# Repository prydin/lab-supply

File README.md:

# Linear 0-30V, 2A lab power supply

## Disclaimer

This supply has been built and tested and does work. However, I am a hobbyist doing this to learn. You are
welcome to follow along, but keep the experimental status in mind and always exercise caution when dealing
with electricity!

## Abstract

This project aims to design a high-performance, high-stability microcontroller-based lab power supply. I am
mostly doing this to learn, but also because I'm tired of cheap switchmode power supplies delivering power
riddled with RF noise.

## Principle of operation

### High voltage section

The high voltage section is very simple and consists of a regular AC inlet with a safety capacitor across it.
There is a 3A fuse in series with the hot lead and a two pole mains switch. The transformer is a 24V/4A unit
with a 12V center tap. Once rectified, the voltage reaches about 36V at my location. Mains ground is connected
to the chassis as well as the ground output terminal.

### Analog secion

32-36V AC enters the circuit at the `AC1` and `AC2` terminals and gets rectified and smoothed into approximately
36-40V DC. This voltage is then pre-regulated down to 32V through `Q3` which is gets its voltage reference the
backwards bias of `D3`. This voltage is used to power the opamps. The `CNT` input is the transformer center tap,
which should be around 15V and is used to create the +12V and +5V voltages.

The `U1D` opamp acts as a voltage regulation amplifier and expects a control voltage between 0-4.096V on its postive input. The feedback loop is tuned
to 7.32x amplification, resulting in an output voltage ranging from 0-30V. The Darlington pair at `Q3` acts
as a emitter follower current amplifier.

Current regulation is based on a high-side current sensing resistor, `R27`. The differential voltage across the
current sense resistor is amplified to a 0-2.5V signal using an INA225 current sense amplifier. This voltage is
then sent to the positivie input of `U1A`. The control circuitry feeds a 0-4.096V signal
to the `V_ISET` input, which is scaled down to 0-2.5V through a resistor network. This voltage is then fed to the
negative input of `U1A`. When the voltage from the current sense amplifier goes above the control voltage on the negative input,
the opamp will source current to Q2, which brings the base on Q3 low until the current is limited to the
set value. `Q3` is needed since we want to keep R24 relatively low to avoid voltage drop at high output currents,
while making sure `U1A` isn't sourcing or sinking too much current. `Q1` acts as a simple switch for turning on
the current limit indicator LED.

### Digital section

The digital section is based on a Adafruit ItsyBitsy 5V, which is essentially an Atmel ATMega 32u4 with some
support circuitry. This was chosen to simplify the design and keep everything as through hole. The digital
section is responsible for feeding the `V_VSET` and `V_ISET` voltages to the the analog section, as well
as measuring and presenting actual voltages and currents.

A key component is the LMZ4040DBZ voltage reference, which provides a stable 4.096V reference used by the
rest of the circuit.

The control voltages are generated by an MPC4922 12-bit DAC and fed directly to the analog section. The user
sets the desired voltage and current using two rotary encoders which can be pushed to switch between a "fine"
and "coarse" mode.

The output voltage of the supply is measured by an MCP3202 ADC through a voltage divider network to bring the
voltage down to 0-4.096V. Further overvoltage protection is offered by the `D12` clamping diode. Current is
measured in a similar way, but since that signal is in the 0-1V range, it is first amplified 4.096x by `U1B`.
This signal is also clamped to the 4.096V reference through `D10`.

## Controls

### Current and voltage

Current and voltage are controlled using two rotary encoders. Pressing the knob switches between coarse and fine
mode. In coarse mode, a blinking cursor will indicate the least significant digit subject to change by turning
the knob.

### Enable/disable

The enable switch enables or disables the output. Notice that this is a "soft" disable that's simply shorting
the posisitive terminal on the voltage regulation opamp to ground. Thus, the output is NOT electrically isolated
from the rest of the circuit.

### Lock mode

When the lock switch is activated, voltage and current output are locked to their current values. The user can
still change the settings, but they are not acted upon. When the switch is flipped, the voltage and current
output is changed to the current setting. This is useful when a user is carefully dialing in new settings
without changing the output while turning the knobs. When locked mode is activated, the "->" symbol between
set and actual values on the display is changed to "LCK".

## Grounding

This power supply is designed to be floating, i.e. it is isolated from ground. If the user needs either
output (plus or minus) to be grounded, they may simply short it to ground using a ground bar or patch
wire. Since the supply uses high side current sense, accidental shorts to ground should not cause damage.

## Physical design and enclosure

### PCB design

This is my very first PCB design and there are many beginners mistakes present in the design. However, it
does work. If I ever redesign this, I would make the +36V path shorter, for example. There are also some
questionable component placements. As with any open source project, you are encouraged to improve on it!

### Enclosure

I opted for a cheap sheet metal/plastic box that is widely available on sites like Ali Express and Amazon.
It works well, but the metal is fairly thin and tends to flex when unplugging the leads.

### Cooling

The TIP142 output transistor requires good cooling. I opted for a simple $9 AMD CPU cooler and bolted the
transistor and the 7805 regulator to it. I'm currently using isolating pads for the TIP142, but I'm not
entirely happy with the heat transfer. I might remove that, although I'm not sure I like to have unregulated 36V
exposed inside the case. The fan is PWM controlled using a simple temperature curve algorithm.

### Rotary encoders and switches

The rotary encoders and switches (with exception of the mains switch) are all cheap Amazon products and work
well so far.

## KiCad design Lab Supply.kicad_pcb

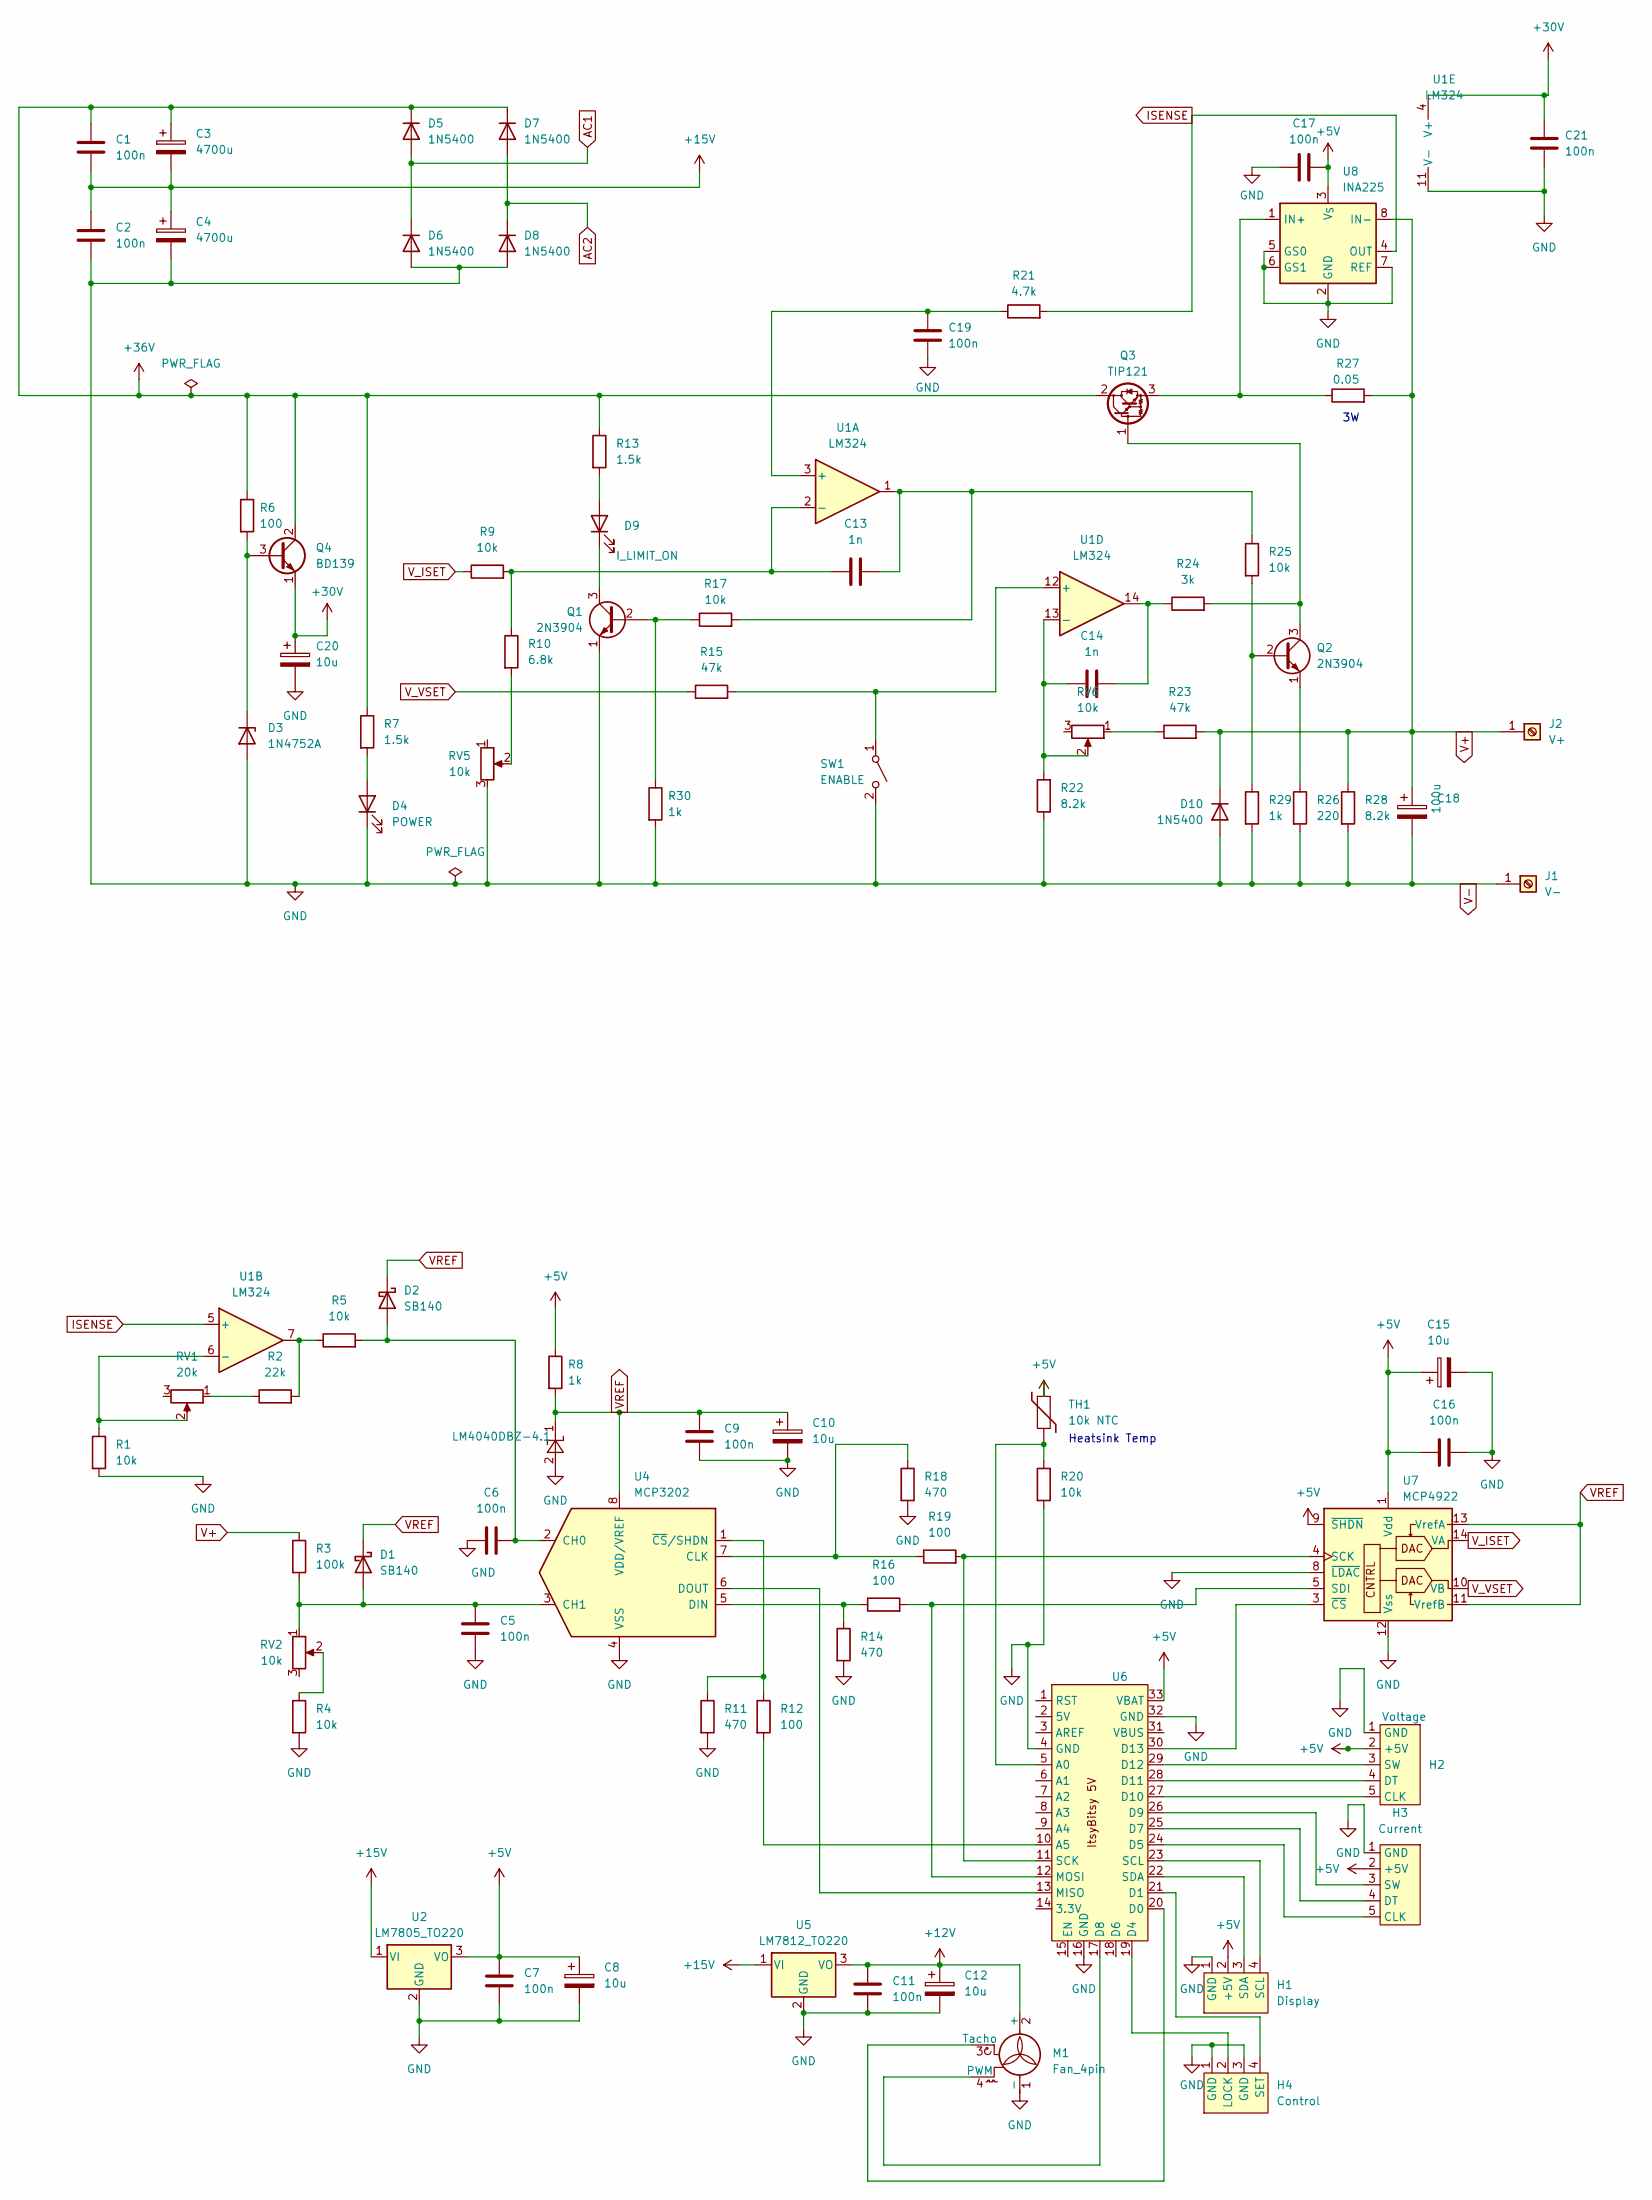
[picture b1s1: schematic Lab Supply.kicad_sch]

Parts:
C1, C2, C5, C6, C7, C9, C11, C16, C17, C19, C21: 100n; C_Disc_D3.4mm_W2.1mm_P2.50mm
C3, C4: 4700u; CP_Radial_D18.0mm_P7.50mm
C8, C10, C12, C15, C20: 10u; CP_Radial_D4.0mm_P1.50mm
C13, C14: 1n; C_Disc_D3.4mm_W2.1mm_P2.50mm
C18: 100u; CP_Radial_D8.0mm_P3.50mm
D1, D2: SB140; D_DO-41_SOD81_P10.16mm_Horizontal
D3: 1N4752A; D_DO-41_SOD81_P5.08mm_Vertical_KathodeUp
D4: POWER; PinHeader_1x02_P2.54mm_Vertical
D5, D6, D7, D8, D10: 1N5400; D_DO-201AD_P12.70mm_Horizontal
D9: I_LIMIT_ON; PinHeader_1x02_P2.54mm_Vertical
H1: Display; PinHeader_1x04_P2.54mm_Vertical
H2: Voltage; PinHeader_1x05_P2.54mm_Vertical
H3: Current; PinHeader_1x05_P2.54mm_Vertical
H4: Control; PinHeader_1x04_P2.54mm_Vertical
J1: V-
J2: V+
M1: Fan_4pin; Molex_KK-254_AE-6410-04A_1x04_P2.54mm_Vertical
Q1, Q2: 2N3904; TO-92_Inline
Q3: TIP121; TO-220-3_Vertical
Q4: BD139; TO-126-3_Vertical
R1, R4, R5, R9, R17, R20, R25: 10k; R_Axial_DIN0204_L3.6mm_D1.6mm_P7.62mm_Horizontal
R2: 22k; R_Axial_DIN0204_L3.6mm_D1.6mm_P7.62mm_Horizontal
R3: 100k; R_Axial_DIN0204_L3.6mm_D1.6mm_P7.62mm_Horizontal
R6, R12, R16, R19: 100; R_Axial_DIN0204_L3.6mm_D1.6mm_P7.62mm_Horizontal
R7, R13: 1.5k; R_Axial_DIN0204_L3.6mm_D1.6mm_P7.62mm_Horizontal
R8, R29, R30: 1k; R_Axial_DIN0204_L3.6mm_D1.6mm_P7.62mm_Horizontal
R10: 6.8k; R_Axial_DIN0204_L3.6mm_D1.6mm_P7.62mm_Horizontal
R11, R14, R18: 470; R_Axial_DIN0204_L3.6mm_D1.6mm_P7.62mm_Horizontal
R15, R23: 47k; R_Axial_DIN0204_L3.6mm_D1.6mm_P7.62mm_Horizontal
R21: 4.7k; R_Axial_DIN0204_L3.6mm_D1.6mm_P7.62mm_Horizontal
R22, R28: 8.2k; R_Axial_DIN0204_L3.6mm_D1.6mm_P7.62mm_Horizontal
R24: 3k; R_Axial_DIN0204_L3.6mm_D1.6mm_P7.62mm_Horizontal
R26: 220; R_Axial_DIN0204_L3.6mm_D1.6mm_P7.62mm_Horizontal
R27: 0.05; R_Axial_DIN0207_L6.3mm_D2.5mm_P10.16mm_Horizontal
RV1: 20k; TRIM_3362P-1-253LF
RV2, RV5, RV6: 10k; TRIM_3362P-1-253LF
SW1: ENABLE; PinHeader_1x02_P2.54mm_Vertical
TH1: 10k NTC; PinHeader_1x02_P2.54mm_Vertical
U1: LM324; DIP-14_W7.62mm
U2: LM7805_TO220; TO-220-3_Vertical
U3: LM4040DBZ-4.1; TO-92_HandSolder
U4: MCP3202; DIP-8_W7.62mm
U5: LM7812_TO220; TO-220-3_Vertical
U6: Itsy Bitsy 5V
U7: MCP4922; DIP-14_W7.62mm
U8: INA225; VSSOP-8_3.0x3.0mm_P0.65mm

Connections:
+5V: C7.1, C8.1, C15.1, C16.1, C17.2, H1.2 (+5V), H2.2 (+5V), H3.2 (+5V), R8.1, TH1.1, U2.3 (VO), U6.33 (VBAT), U7.1 (Vdd), U7.9 (~SHDN), U8.3 (V_{S})
+12V: C11.1, C12.1, M1.2 (+), U5.3 (VO)
+15V: C1.2, C2.1, C3.2, C4.1, J1.2, U2.1 (VI), U5.1 (VI)
+28V: C20.1, C21.1, Q4.1 (E), U1.4 (V+)
+36V: C1.1, C3.1, D5.1 (K), D7.1 (K), Q3.2 (C), Q4.2 (C), R6.1, R7.1, R13.1
AC2: D7.2 (A), D8.1 (K), J1.3
ISENSE: R21.2, U1.5 (+), U8.4 (OUT)
unnamed: C13.2, R17.2, R25.1, U1.1
unnamed: C14.1, R24.1, U1.14
unnamed: C5.1, D1.2 (A), R3.2, RV2.1, U4.3 (CH1)
unnamed: C6.2, D2.2 (A), R5.2, U4.2 (CH0)
unnamed: D3.1 (K), Q4.3 (B), R6.2
unnamed: D4.2 (A), R7.2
unnamed: D9.2 (A), R13.2
unnamed: D9.1 (K), Q1.3 (C)
unnamed: H1.4 (SCL), U6.23 (SCL)
unnamed: H1.3 (SDA), U6.22 (SDA)
unnamed: H2.5 (CLK), U6.27 (D10)
unnamed: H2.4 (DT), U6.28 (D11)
unnamed: H2.3 (SW), U6.29 (D12)
unnamed: H3.5 (CLK), U6.24 (D5)
unnamed: H3.4 (DT), U6.25 (D7)
unnamed: H3.3 (SW), U6.26 (D9)
unnamed: H4.2 (LOCK), U6.19 (D4)
unnamed: H4.4 (SET), U6.21 (D1)
unnamed: M1.4 (PWM), U6.17 (D8)
unnamed: M1.3 (Tacho), U6.20 (D0)
unnamed: Q1.2 (B), R17.1, R30.1
unnamed: Q2.2 (B), R25.2, R29.1
unnamed: Q2.3 (C), Q3.1 (B), R24.2
unnamed: Q2.1 (E), R26.1
unnamed: Q3.3 (E), R27.1, U8.1 (IN+)
unnamed: R2.1, RV1.1
unnamed: R2.2, R5.1, U1.7
unnamed: R4.1, RV2.2
unnamed: R10.2, RV5.2
unnamed: R23.1, RV6.1
unnamed: R15.2, SW1.1 (A), U1.12 (+)
unnamed: C19.1, R21.1, U1.3 (+)
unnamed: C13.1, R9.2, R10.1, U1.2 (-)
unnamed: R1.1, RV1.2, U1.6 (-)
unnamed: C14.2, R22.2, RV6.2, U1.13 (-)
unnamed: R18.1, R19.1, U4.7 (CLK)
unnamed: R14.1, R16.1, U4.5 (DIN)
unnamed: U4.6 (DOUT), U6.13 (MISO)
unnamed: R11.1, R12.1, U4.1 (~CS/SHDN)
unnamed: R20.1, TH1.2, U6.5 (A0)
unnamed: R12.2, U6.10 (A5)
unnamed: U6.30 (D13), U7.3 (~CS)
unnamed: R16.2, U6.12 (MOSI), U7.5 (SDI)
unnamed: R19.2, U6.11 (SCK), U7.4 (SCK)
V+: C18.1, D10.1 (K), J2.1, R3.1, R23.2, R27.2, R28.1, U8.8 (IN-); also elsewhere on the board
VREF: C9.1, C10.1, D1.1 (K), D2.1 (K), R8.2, U3.1 (K), U4.8 (VDD/VREF), U7.11 (VrefB), U7.13 (VrefA)
V_ISET: R9.1, U7.14 (VA)
V_VSET: R15.1, U7.10 (VB)

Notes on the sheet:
Heatsink Temp

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
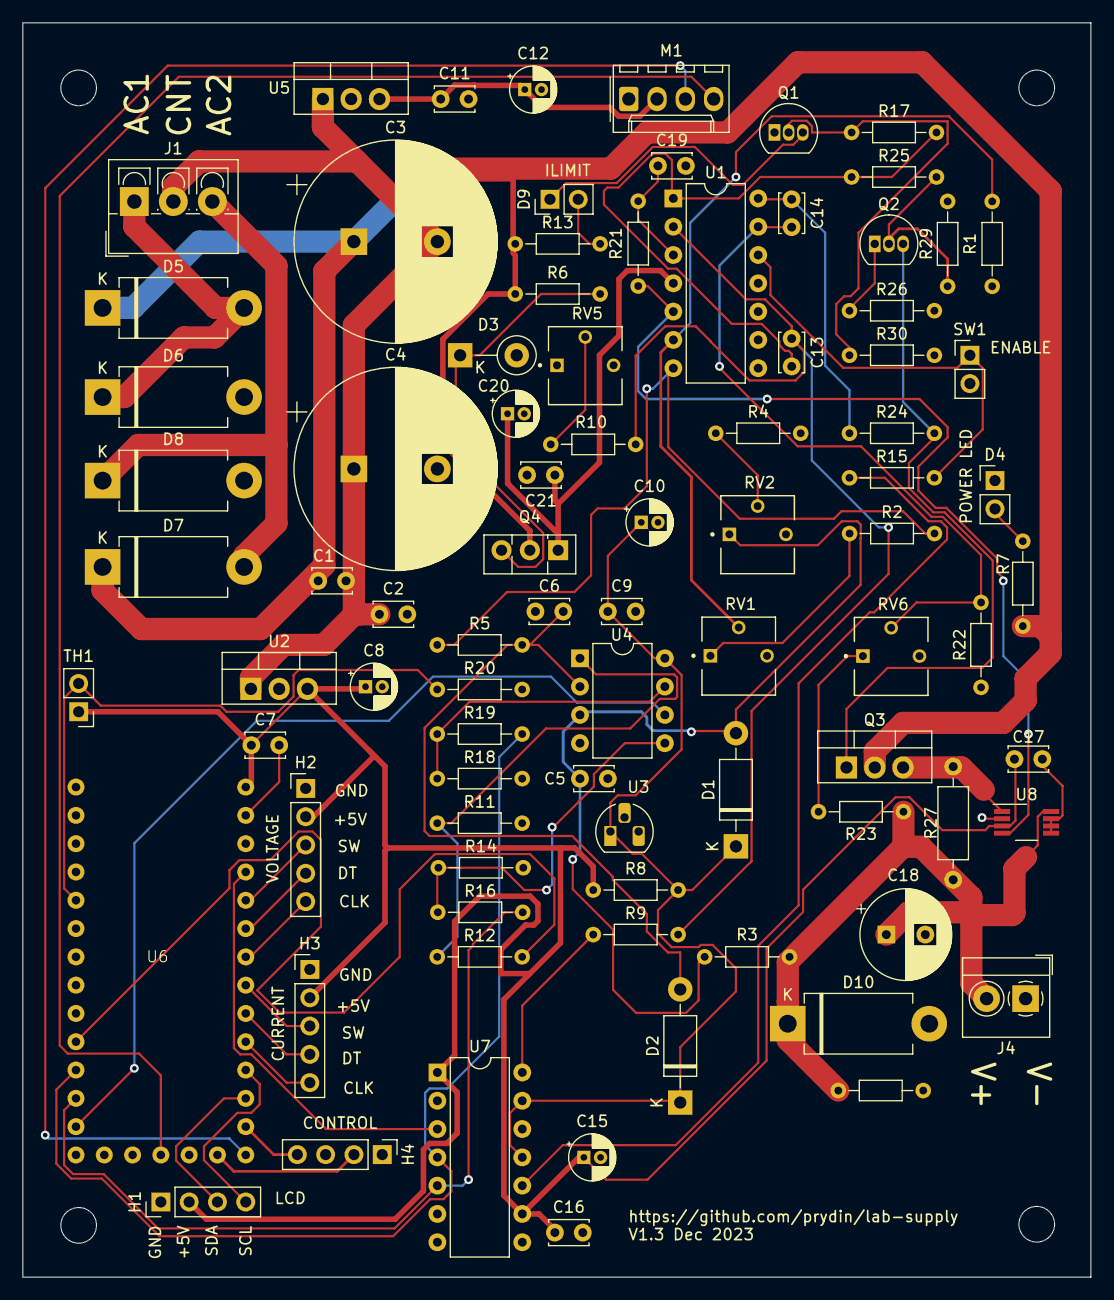
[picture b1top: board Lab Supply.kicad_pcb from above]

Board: 2 copper layers, 95.9 x 112.6 mm, 86 parts (0 on the bottom side), 57 nets.

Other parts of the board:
J4: OUTPUT; TerminalBlock_4Ucon_1x02_P3.50mm_Horizontal

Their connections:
V+: J4.2; also elsewhere on the board

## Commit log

2023-10-22 Changed to LM324
2023-10-22 Redesigned CC indicator
2023-10-23 Added DA cinverter
2023-10-27 Started working on firmware
2023-10-30 Finished up display code
2023-11-01 Rearranged firmware code
2023-11-02 Added README
2023-11-02 Changed background color of schematic
2023-11-02 Fixed README
2023-11-03 Fixed ADC stuff and optimized display updates
2023-11-03 Cleanup
2023-11-03 Corrected reversed display header
2023-11-04 Added fan control
2023-11-06 Implemented RPM measurement
2023-12-15 Added gerber
2023-12-15 Added new images
2023-12-15 Added 3d model
2023-12-26 Added voltage calibration
2023-12-26 First working version
2023-12-27 Added lock mode
2023-12-27 Cleaned up documentation. Minor PCB changes
2023-12-27 Fixed minor README issue
2023-12-27 Updated schema image
